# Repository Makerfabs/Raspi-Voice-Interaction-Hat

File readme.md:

# Raspi Voice Interaction Hat

```c++
/*
Version:		V1.0
Author:			Vincent
Create Date:	2020/11/4
Note:

*/
```

[toc]

# OVERVIEW

## Introduce

[Makerfabs home page](https://www.makerfabs.com/)

[Makerfabs Wiki](https://makerfabs.com/wiki/index.php?title=Main_Page)

Voice Interaction Hat for Raspberry Pi is an expansion board designed for Raspberry Pi, which provides voice input and audio output, can be used in AI and voice applications.

[wiki link](https://www.makerfabs.com/wiki/index.php?title=Voice_Interaction_Hat)

## Features

- WM8960, the low power, high-quality stereo CODEC.
- 2 analog microphones.
- More than 1 meters radius voice capture
- 3W power speaker.
- Provides 3 additional buttons.
- Support Raspberry Pi Zero, Raspberry Pi 1 B+, Pi 2 B, Pi 3 B, Pi 3 B+.

# Driver

## Use voice card driver from seeed : [seeed-voicecard](https://github.com/respeaker/seeed-voicecard)

*The product is designed with reference to the ReSpeaker 4 Mic Array product of seeed. When using Raspberry Pi to drive this expansion board, you can use the seeed driver to drive it to work.*

This sound card is consistent with [ReSpeaker Mic Hat](https://github.com/respeaker/seeed-voicecard#respeaker-mic-hat).

Get the seeed voice card source code. and install all linux kernel drivers

```
git clone https://github.com/respeaker/seeed-voicecard
cd seeed-voicecard
sudo ./install.sh
sudo reboot
```

Check that the sound card name matches the source code seeed-voicecard.

```
#for ReSpeaker 2-mic
pi@raspberrypi:~/seeed-voicecard $ aplay -l
**** List of PLAYBACK Hardware Devices ****
card 0: ALSA [bcm2835 ALSA], device 0: bcm2835 ALSA [bcm2835 ALSA]
  Subdevices: 8/8
  Subdevice #0: subdevice #0
  Subdevice #1: subdevice #1
  Subdevice #2: subdevice #2
  Subdevice #3: subdevice #3
  Subdevice #4: subdevice #4
  Subdevice #5: subdevice #5
  Subdevice #6: subdevice #6
  Subdevice #7: subdevice #7
card 0: ALSA [bcm2835 ALSA], device 1: bcm2835 ALSA [bcm2835 IEC958/HDMI]
  Subdevices: 1/1
  Subdevice #0: subdevice #0
card 1: seeed2micvoicec [seeed-2mic-voicecard], device 0: bcm2835-i2s-wm8960-hifi wm8960-hifi-0 []
  Subdevices: 1/1
  Subdevice #0: subdevice #0
pi@raspberrypi:~/seeed-voicecard $ arecord -l
**** List of CAPTURE Hardware Devices ****
card 1: seeed2micvoicec [seeed-2mic-voicecard], device 0: bcm2835-i2s-wm8960-hifi wm8960-hifi-0 []
  Subdevices: 1/1
  Subdevice #0: subdevice #0
pi@raspberrypi:~/seeed-voicecard $ 
```

# How To Use

## Record

```bash
arecord  -c 2 -r 16000 -f S16_LE -Dhw:1,0 -d 5 result.wav
```

16 KHZ, 16bit, 2 channel, 5 second recording.

## Play

```bash
aplay -Dhw:1,0 result.wav
```

Play wav format files.

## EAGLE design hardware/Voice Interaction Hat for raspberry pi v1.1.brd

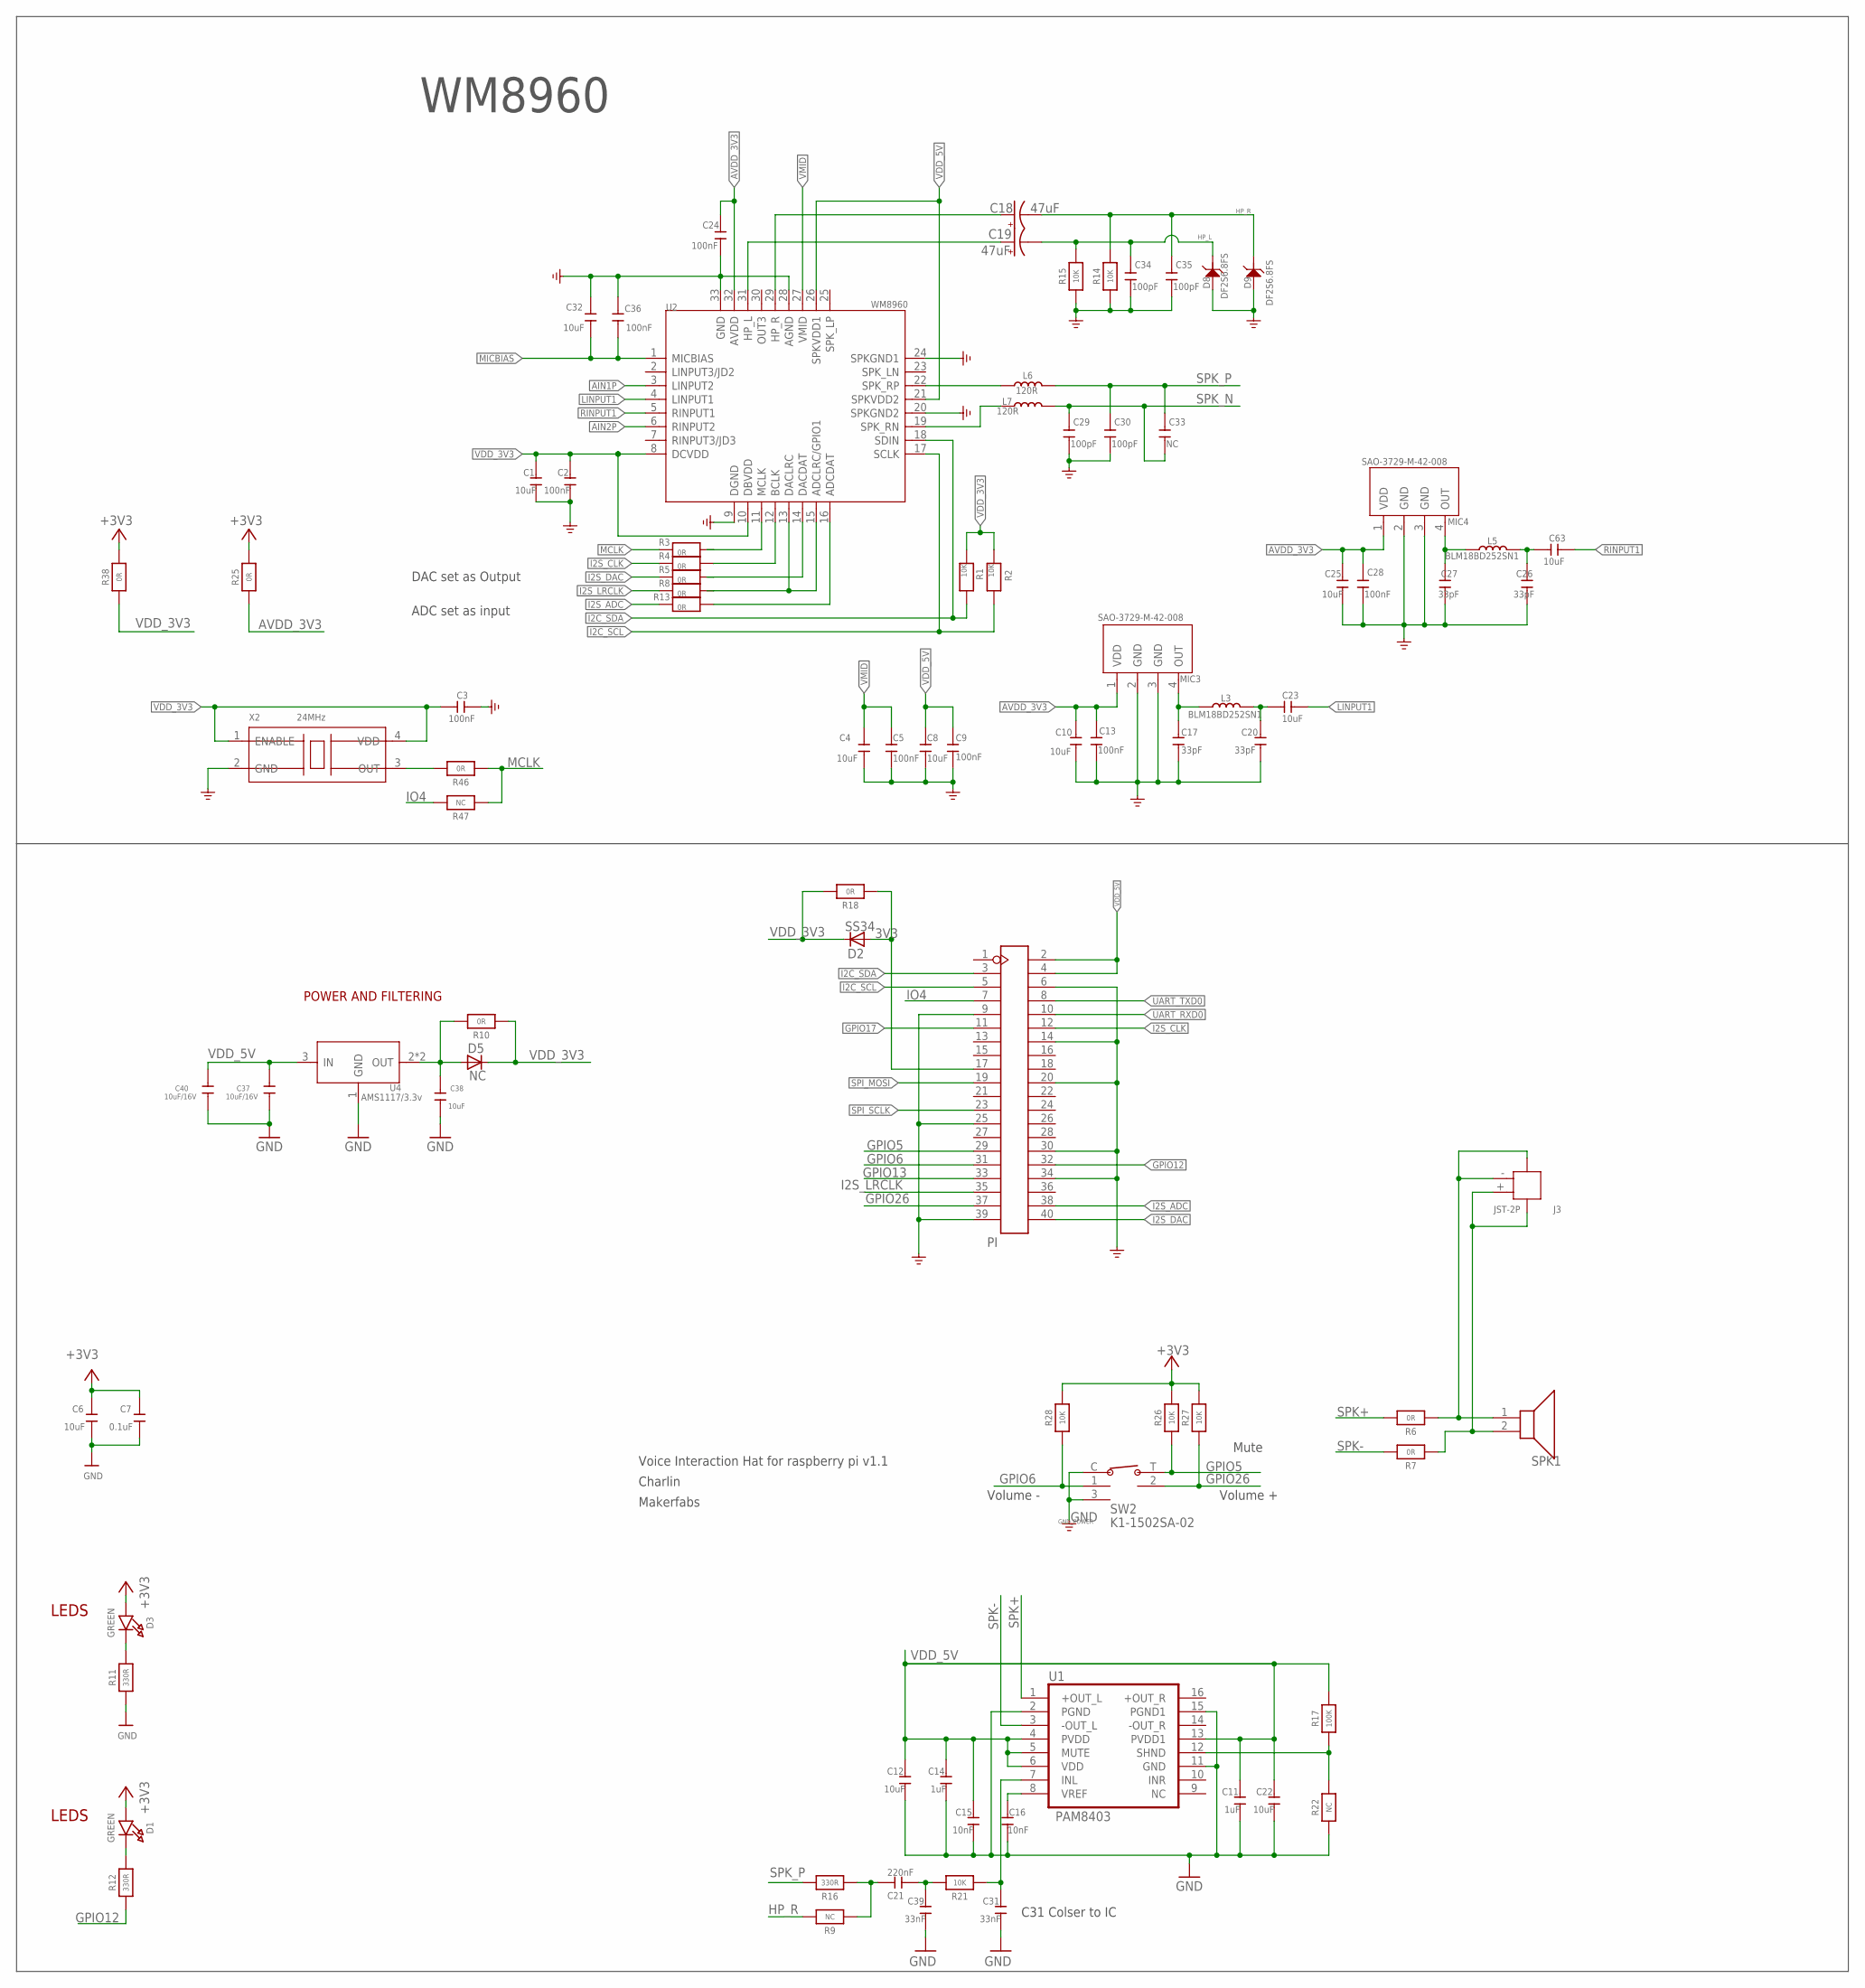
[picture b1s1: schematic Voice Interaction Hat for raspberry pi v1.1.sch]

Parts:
C1, C6, C12, C22: 10uF; DISCRETE_C0603
C2, C3, C24, C36: 100nF; DISCRETE_C0603
C4, C8, C10, C23, C25, C32, C63: 10uF; C0603
C5, C9, C13, C28: 100nF; C0603
C7: 0.1uF; DISCRETE_C0603
C11, C14: 1uF; DISCRETE_C0603
C15, C16: 10nF; DISCRETE_C0603
C17, C20, C26, C27: 33pF; C0603
C18, C19: 47uF; EIA3528
C21: 220nF; DISCRETE_C0603
C29, C30, C34, C35: 100pF; C0603
C31, C39: 33nF; DISCRETE_C0603
C33: NC; C0603
C37, C40: 10uF/16V; 0603
C38: 10uF; 0603
D1, D3: GREEN; CHIPLED_0805_NOOUTLINE
D2: SS34; DO-214AC
D5: NC; DO-214AC
D8, D9: DF2S6.8FS; SOD-923
J3: JST-2P; HW2-SMD-2.0-90D
L3, L5: BLM18BD252SN1; L0603
L6, L7: 120R; L0603
MIC3, MIC4: SAO-3729-M-42-008; MIC4-SMD-3.76X2.95MM
PI: HEADER-2X20P1; DIP-2X20-2.54MM
R1, R2, R14, R15, R21, R26, R27, R28: 10K; 0603-NO
R3, R4, R5, R6, R7, R8, R10, R13, R18, R25, R38, R46: 0R; 0603-NO
R9, R22, R47: NC; 0603-NO
R11, R12, R16: 330R; 0603-NO
R17: 100K; 0603-NO
SPK1: SPK; SPK-SMD2-5000L3000W
SW2: K1-1502SA-02; SMD5-60P-1180L1170W
U1: PAM8403; SOP-16
U2: WM8960; QFN32G-0.5-5X5MM
U4: AMS1117/3.3v; SOT89
X2: 24MHz; OSC4-SMD-2.5X2.0X0.8MM

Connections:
3V3: D2.A, PI.17, R18.1
$123: C18.A (+), U2.29 (HP_R)
$124: C19.A (+), U2.31 (HP_L)
+3V3: C6.2, C7.2, D1.A, D3.A, R25.2, R26.2, R27.2, R28.2, R38.2
AIN1P: U2.3 (LINPUT2)
AIN2P: U2.6 (RINPUT2)
AUDIO_SHDN: R17.1, R22.2, U1.12 (SHND)
AVDD_3V3: C10.1, C13.1, C24.2, C25.1, C28.1, MIC3.1 (VDD), MIC4.1 (VDD), R25.1, U2.32 (AVDD)
GND: C1.1, C2.1, C3.1, C4.2, C5.2, C6.1, C7.1, C8.2, C9.2, C10.2, C11.1, C12.1, C13.2, C14.1, C15.1, C16.1, C17.2, C20.2, C22.1, C24.1, C25.2, C26.2, C27.2, C28.2, C29.2, C30.2, C31.1, C32.1, C34.2, C35.2, C36.2, C37.2, C38.2, C39.1, C40.2, D8.2 (1), D9.2 (1), MIC3.2 (GND), MIC3.3 (GND), MIC4.2 (GND), MIC4.3 (GND), PI.6, PI.9, PI.14, PI.20, PI.25, PI.30, PI.34, PI.39, R11.1, R14.1, R15.1, R22.1, SW2.3, SW2.C, U1.2 (PGND), U1.11 (GND), U1.15 (PGND1), U2.9 (DGND), U2.20 (SPKGND2), U2.24 (SPKGND1), U2.28 (AGND), U2.33 (GND), U4.1 (GND), X2.2 (GND)
GPIO5: PI.29, R26.1, SW2.T
GPIO6: PI.31, R28.1, SW2.1
GPIO12: PI.32, R12.1
GPIO13: PI.33
GPIO17: PI.11
GPIO26: PI.37, R27.1, SW2.2
HP_L: C19.C (-), C34.1, D8.1 (2), R15.2
HP_R: C18.C (-), C35.1, D9.1 (2), R9.2, R14.2
I2C_SCL: PI.5, R2.1, U2.17 (SCLK)
I2C_SDA: PI.3, R1.1, U2.18 (SDIN)
I2S_ADC: PI.38, R13.2
I2S_CLK: PI.12, R4.2
I2S_DAC: PI.40, R5.2
I2S_LRCLK: PI.35, R8.2
IO4: PI.7, R47.2
LINPUT1: C23.2, U2.4 (LINPUT1)
MCLK: R3.2, R46.1, R47.1
MICBIAS: C32.2, C36.1, U2.1 (MICBIAS)
unnamed: C38.1, D5.A, R10.2, U4.2 (OUT), U4.4 (OUT)
unnamed: D1.C, R12.2
unnamed: C31.2, R21.1, U1.7 (INL)
unnamed: D3.C, R11.2
unnamed: J3.3, J3.- (2), R6.1, SPK1.1
unnamed: C21.1, C39.2, R21.2
unnamed: J3.4, J3.+ (1), R7.1, SPK1.2
unnamed: R5.1, U2.14 (DACDAT)
unnamed: C20.1, C23.1, L3.2
unnamed: C17.1, L3.1, MIC3.4 (OUT)
unnamed: C26.1, C63.1, L5.2
unnamed: C16.2, U1.8 (VREF)
unnamed: R46.2, X2.3 (OUT)
unnamed: C27.1, L5.1, MIC4.4 (OUT)
unnamed: R13.1, U2.16 (ADCDAT)
unnamed: R8.1, U2.13 (DACLRC), U2.15 (ADCLRC/GPIO1)
unnamed: R4.1, U2.12 (BCLK)
unnamed: R3.1, U2.11 (MCLK)
unnamed: L6.1, U2.22 (SPK_RP)
unnamed: L7.1, U2.19 (SPK_RN)
unnamed: C21.2, R9.1, R16.1
RINPUT1: C63.2, U2.5 (RINPUT1)
SPI_MOSI: PI.19
SPI_SCLK: PI.23
SPK+: R6.2, U1.1 (+OUT_L)
SPK-: R7.2, U1.3 (-OUT_L)
SPK_N: C29.1, C33.2, L7.2
SPK_P: C30.1, C33.1, L6.2, R16.2
UART_RXD0: PI.10
UART_TXD0: PI.8
VDD_3V3: C1.2, C2.2, C3.2, D2.C, D5.C, R1.2, R2.2, R10.1, R18.2, R38.1, U2.8 (DCVDD), U2.10 (DBVDD), X2.1 (ENABLE), X2.4 (VDD)
VDD_5V: C8.1, C9.1, C11.2, C12.2, C14.2, C15.2, C22.2, C37.1, C40.1, PI.2, PI.4, R17.2, U1.4 (PVDD), U1.5 (MUTE), U1.6 (VDD), U1.13 (PVDD1), U2.21 (SPKVDD2), U2.26 (SPKVDD1), U4.3 (IN)
VMID: C4.1, C5.1, U2.27 (VMID)

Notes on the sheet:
Voice Interaction Hat for raspberry pi v1.1
LEDS
Charlin
Volume +
Volume -
Mute
Makerfabs
WM8960
DAC set as Output
ADC set as input
POWER AND FILTERING
C31 Colser to IC

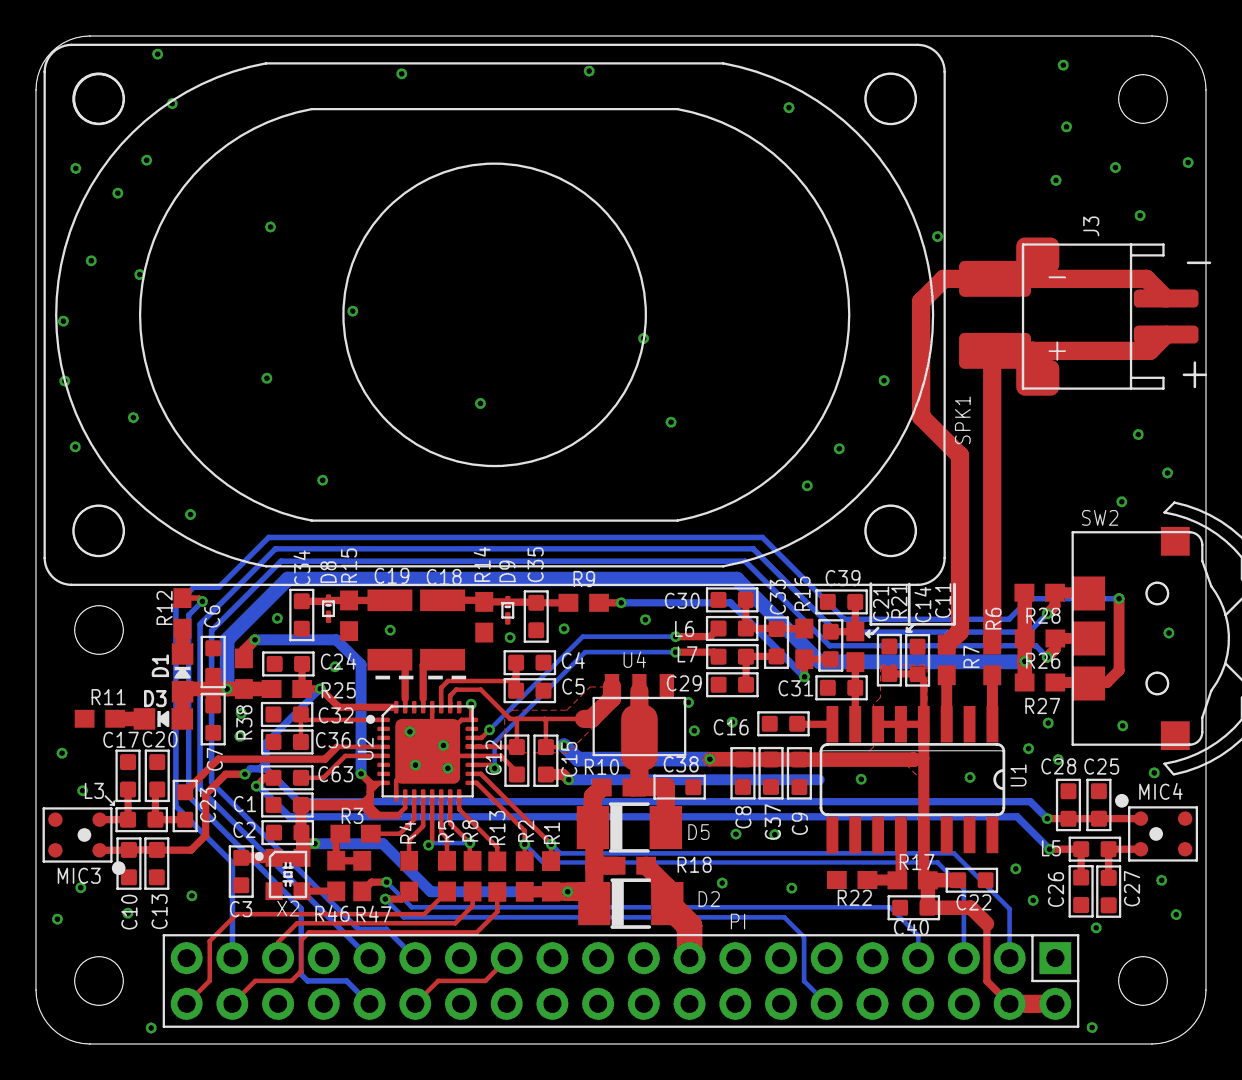
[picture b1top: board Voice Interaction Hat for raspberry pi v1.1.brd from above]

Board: 2 copper layers, 64.9 x 55.9 mm, 89 parts (1 on the bottom side), 52 nets.

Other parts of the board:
U$1: MAKERFABS_0.3

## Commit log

2020-11-04 Create
2020-11-10 addfile

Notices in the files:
parts and their libraries:
microbuilder: This work is placed in the public domain, and may be freely used for commercial and non-commercial work with the following conditions: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
SparkFun-Capacitors: Licensing: Creative Commons ShareAlike 4.0 International - https://creativecommons.org/licenses/by-sa/4.0
